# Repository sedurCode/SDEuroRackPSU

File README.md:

View this project on [CADLAB.io](https://cadlab.io/project/1465). 

EuroRack PSU

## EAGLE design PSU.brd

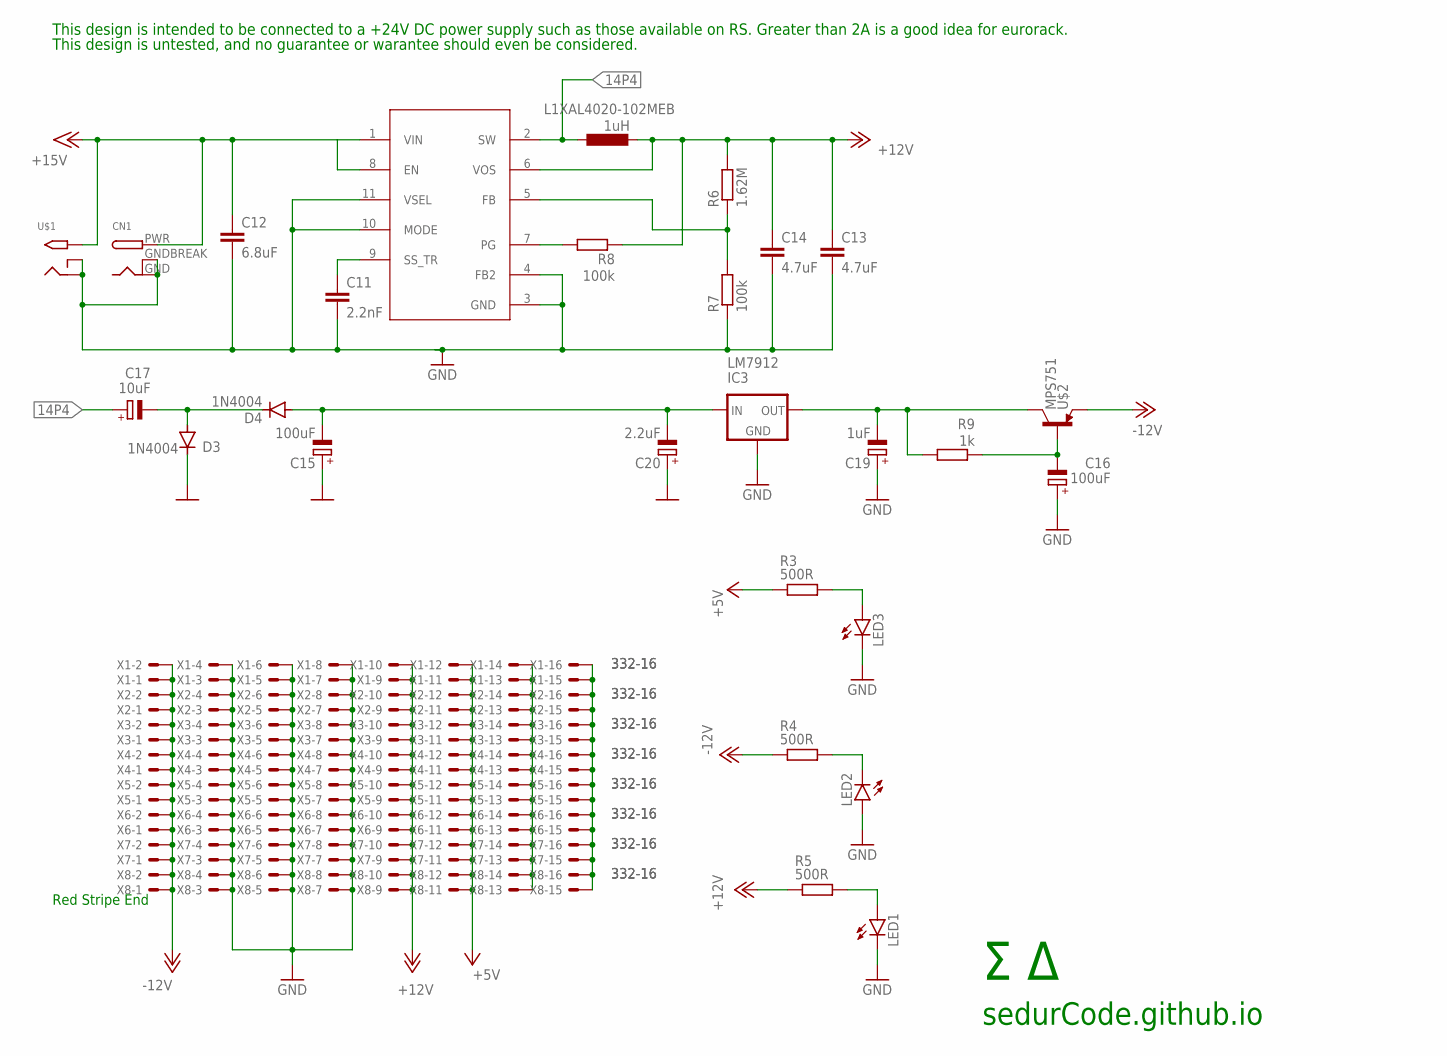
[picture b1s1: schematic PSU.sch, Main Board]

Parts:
C11: 2.2nF; C0805
C12: 6.8uF; C0805
C13, C14: 4.7uF; C0805
C15, C16: 100uF; PANASONIC_B
C17: 10uF; PANASONIC_B
C19: 1uF; PANASONIC_B
C20: 2.2uF; PANASONIC_B
CN1: DCBARRELPTH; DCJACK_2MM_PTH
D3, D4: 1N4004; DO41-10
IC3: LM7912; 79XXL
L1XAL4020-102MEB: 1uH; L5038P
LED1, LED2, LED3: LED5MM
R3, R4, R5: 500R; 0207/7
R6: 1.62M; R0805
R7, R8: 100k; R0805
R9: 1k; R0805
U2: Value; RGX0011A
U$1: 2.1MMJACKTHM; PJ-102A
U$2: MPS751; TO92-EBC
X1, X2, X3, X4, X5, X6, X7, X8: 332-16

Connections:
10: U2.8 (EN)
14P4: C17.+, L1XAL4020-102MEB.1, U2.2 (SW)
+5V: R3.1, X1.11, X1.12, X2.11, X2.12, X3.11, X3.12, X4.11, X4.12, X5.11, X5.12, X6.11, X6.12, X7.11, X7.12, X8.11, X8.12
+12V: C13.1, C14.1, L1XAL4020-102MEB.2, R5.1, R6.2, R8.1, U2.6 (VOS), X1.9, X1.10, X2.9, X2.10, X3.9, X3.10, X4.9, X4.10, X5.9, X5.10, X6.9, X6.10, X7.9, X7.10, X8.9, X8.10
+15V: C12.1, CN1.PWR, U2.1 (VIN), U$1.TIP
-12V: R4.1, U$2.E, X1.1, X1.2, X2.1, X2.2, X3.1, X3.2, X4.1, X4.2, X5.1, X5.2, X6.1, X6.2, X7.1, X7.2, X8.1, X8.2
GND: C11.2, C12.2, C13.2, C14.2, C15.+, C16.+, C19.+, C20.+, CN1.GND, CN1.GNDBREAK, D3.C, IC3.GND, LED1.K (C), LED2.A, LED3.K (C), R7.1, U2.3 (GND), U2.4 (FB2), U2.10 (MODE), U2.11 (VSEL), U$1.RING, U$1.RING_SW, X1.3, X1.4, X1.5, X1.6, X1.7, X1.8, X2.3, X2.4, X2.5, X2.6, X2.7, X2.8, X3.3, X3.4, X3.5, X3.6, X3.7, X3.8, X4.3, X4.4, X4.5, X4.6, X4.7, X4.8, X5.3, X5.4, X5.5, X5.6, X5.7, X5.8, X6.3, X6.4, X6.5, X6.6, X6.7, X6.8, X7.3, X7.4, X7.5, X7.6, X7.7, X7.8, X8.3, X8.4, X8.5, X8.6, X8.7, X8.8
unnamed: R8.2, U2.7 (PG)
unnamed: C15.-, C20.-, D4.A, IC3.IN
unnamed: C19.-, IC3.OUT, R9.2, U$2.C
unnamed: C11.1, U2.9 (SS_TR)
unnamed: R6.1, R7.2, U2.5 (FB)
unnamed: C16.-, R9.1, U$2.B
unnamed: C17.-, D3.A, D4.C
unnamed: LED1.A, R5.2
unnamed: LED2.K (C), R4.2
unnamed: X1.15, X1.16, X2.15, X2.16, X3.15, X3.16, X4.15, X4.16, X5.15, X5.16, X6.15, X6.16, X7.15, X7.16, X8.15, X8.16
unnamed: X1.13, X1.14, X2.13, X2.14, X3.13, X3.14, X4.13, X4.14, X5.13, X5.14, X6.13, X6.14, X7.13, X7.14, X8.13, X8.14
unnamed: LED3.A, R3.2

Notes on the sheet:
Red Stripe End
Σ Δ
sedurCode.github.io
This design is intended to be connected to a +24V DC power supply such as those available on RS. Greater than 2A is a good idea for eurorack.
This design is untested, and no guarantee or warantee should even be considered.

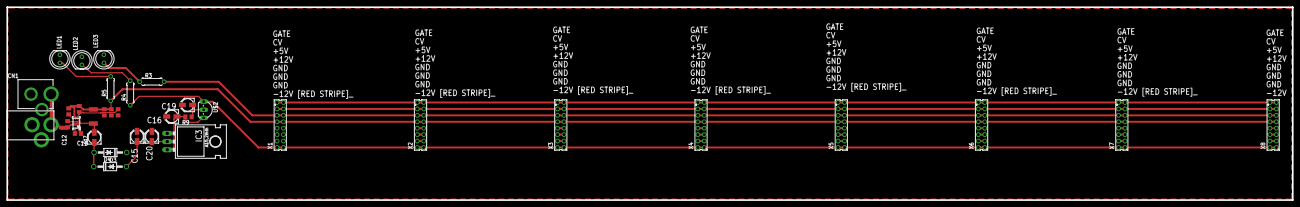
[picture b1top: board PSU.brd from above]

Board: 1 copper layer, 400.0 x 60.0 mm, 35 parts (0 on the bottom side), 18 nets.

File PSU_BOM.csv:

"Part";"Value";"Device";"Package";"Description";"MANUFACTURER";"MANUFACTURER_NAME";"MANUFACTURER_PART_NUMBER";"PARTNUMBER";"REFDES";"SPICEPREFIX";"TYPE";"VALUE";
"C11";"2.2nF";"C-EUC0805";"C0805";"CAPACITOR, European symbol";"";"";"";"";"";"C";"";"";
"C12";"6.8uF";"C-EUC0805";"C0805";"CAPACITOR, European symbol";"";"";"";"";"";"C";"";"";
"C13";"4.7uF";"C-EUC0805";"C0805";"CAPACITOR, European symbol";"";"";"";"";"";"C";"";"";
"C14";"4.7uF";"C-EUC0805";"C0805";"CAPACITOR, European symbol";"";"";"";"";"";"C";"";"";
"C15";"100uF";"CPOL-EUB";"PANASONIC_B";"POLARIZED CAPACITOR, European symbol";"";"";"";"";"";"C";"";"";
"C16";"100uF";"CPOL-EUB";"PANASONIC_B";"POLARIZED CAPACITOR, European symbol";"";"";"";"";"";"C";"";"";
"C17";"10uF";"CPOL-EUB";"PANASONIC_B";"POLARIZED CAPACITOR, European symbol";"";"";"";"";"";"C";"";"";
"C19";"1uF";"CPOL-EUB";"PANASONIC_B";"POLARIZED CAPACITOR, European symbol";"";"";"";"";"";"C";"";"";
"C20";"2.2uF";"CPOL-EUB";"PANASONIC_B";"POLARIZED CAPACITOR, European symbol";"";"";"";"";"";"C";"";"";
"CN1";"";"DCBARRELPTH";"DCJACK_2MM_PTH";"2.0mm DC Barrel Jack";"";"";"";"";"";"X";"";"";
"D3";"1N4004";"1N4004";"DO41-10";"DIODE";"";"";"";"";"";"";"";"";
"D4";"1N4004";"1N4004";"DO41-10";"DIODE";"";"";"";"";"";"";"";"";
"IC3";"LM7912";"79XXL";"79XXL";"VOLTAGE REGULATOR";"";"";"";"";"";"J";"";"";
"L1XAL4020-102MEB";"1uH";"L-EUL5038P";"L5038P";"INDUCTOR, European symbol";"";"";"";"";"";"L";"";"";
"LED1";"";"LED5MM";"LED5MM";"LED";"";"";"";"";"";"";"";"";
"LED2";"";"LED5MM";"LED5MM";"LED";"";"";"";"";"";"";"";"";
"LED3";"";"LED5MM";"LED5MM";"LED";"";"";"";"";"";"";"";"";
"R3";"500R";"R-EU_0207/7";"0207/7";"RESISTOR, European symbol";"";"";"";"";"";"R";"";"";
"R4";"500R";"R-EU_0207/7";"0207/7";"RESISTOR, European symbol";"";"";"";"";"";"R";"";"";
"R5";"500R";"R-EU_0207/7";"0207/7";"RESISTOR, European symbol";"";"";"";"";"";"R";"";"";
"R6";"1.62M";"R-EU_R0805";"R0805";"RESISTOR, European symbol";"";"";"";"";"";"R";"";"";
"R7";"100k";"R-EU_R0805";"R0805";"RESISTOR, European symbol";"";"";"";"";"";"R";"";"";
"R8";"100k";"R-EU_R0805";"R0805";"RESISTOR, European symbol";"";"";"";"";"";"R";"";"";
"R9";"1k";"R-EU_R0805";"R0805";"RESISTOR, European symbol";"";"";"";"";"";"R";"";"";
"U$1";"2.1MMJACKTHM";"2.1MMJACKTHM";"PJ-102A";"2.1mm x 5.5mm THM DC jack with internal switch. Digikey part #PJ-102A, 4UCON part #05537";"";"";"";"";"";"";"";"";
"U$2";"MPS751";"MPS751";"TO92-EBC";"";"";"";"";"";"";"";"";"";
"U2";"Value";"TPS62135RGXR";"RGX0011A";"";"Texas Instruments";"Texas Instruments";"TPS62135RGXR";"TPS62135RGXR";"RefDes";"";"TYPE";"Value";
"X1";"332-16";"332-16";"332-16";"16 Pin - 2mm Dual Row";"";"";"";"";"";"";"";"";
"X2";"332-16";"332-16";"332-16";"16 Pin - 2mm Dual Row";"";"";"";"";"";"";"";"";
"X3";"332-16";"332-16";"332-16";"16 Pin - 2mm Dual Row";"";"";"";"";"";"";"";"";
"X4";"332-16";"332-16";"332-16";"16 Pin - 2mm Dual Row";"";"";"";"";"";"";"";"";
"X5";"332-16";"332-16";"332-16";"16 Pin - 2mm Dual Row";"";"";"";"";"";"";"";"";
"X6";"332-16";"332-16";"332-16";"16 Pin - 2mm Dual Row";"";"";"";"";"";"";"";"";
"X7";"332-16";"332-16";"332-16";"16 Pin - 2mm Dual Row";"";"";"";"";"";"";"";"";
"X8";"332-16";"332-16";"332-16";"16 Pin - 2mm Dual Row";"";"";"";"";"";"";"";"";

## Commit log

2018-11-25 design first comit
2018-11-25 Backlink to CADLAB.io has been added.
2018-11-27 A different approach
2018-11-27 layout update
2018-11-28 added some gerbers
